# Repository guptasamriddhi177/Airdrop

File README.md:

AIRDROP: Smart Environmental Safety & Early Warning System

It is a smart environmental safety and early-warning system designed to monitor surroundings, detect unusual environmental changes and alert people when something doesn't seem right.

AIRDROP combines multiple sensors, ESP32-based modules and a connected dashboard to make environmental monitoring more accessible. The idea is to build something that doesn't just collect sensor readings but can also help people understand when their surroundings might be becoming unsafe.

I started working on AIRDROP because I wanted to explore how affordable electronics and software could be used for real-world safety problems. I wanted to go beyond making another basic temperature or gas detector, so I started developing a system with multiple monitoring modules, a wearable alert concept and a connected application.

Features

• Environmental monitoring using multiple sensors.
• Temperature, humidity and air-quality monitoring.
• Airflow detection.
• Water-leak detection.
• Motion and distance monitoring.
• ESP32-based wireless communication.
• Firebase integration for real-time data updates.
• Dashboard with sensor readings and alerts.
• Risk scoring system with different safety levels.
• Location-based monitoring concept.
• Wearable notifications and SOS functionality.
• Early-warning and forecasting features under development.

Hardware

AIRDROP uses ESP32-based modules to collect information from different sensors.

Main components:

• ESP32-WROOM-32 modules
• BME680 environmental sensor
• MPU6050 motion sensor
• HC-SR04 ultrasonic sensors
• Airflow sensor
• Water-leak sensors
• Custom-designed PCB
• USB power connection

The system is divided into multiple sensor modules so different environmental parameters can be monitored together.

Schematics

Instead of relying entirely on ready-made sensor boards, I worked on a custom PCB design for the system.

The design uses two ESP32-WROOM-32 modules and a combined board architecture. The goal was to make the electronics more organized and suitable for a proper physical assembly.

PCB specifications:

• 4-layer PCB
• 50 × 50 mm board
• USB-powered design
• Two ESP32-WROOM-32 modules
• Custom component placement and routing

3D Assembly

I also worked on the 3D assembly to understand how the different components would fit together physically.

This helped me visualize the overall structure before moving towards the actual hardware build.

Software & Dashboard

The software side of AIRDROP connects the sensor hardware to a Firebase backend.

The dashboard is designed to display environmental readings, safety scores, alerts and location information.

The planned risk classification is:

- Safe: 0–25
- Caution: 26–50
- Warning: 51–75
- Critical: 76–100

I also want to include a map-based monitoring system, historical readings, multilingual support and a rescue mode.

Firmware

The firmware is being developed for the ESP32 modules.

Its main responsibilities include:

• Reading data from connected sensors.
• Processing sensor readings.
• Communicating between modules.
• Sending data to Firebase.
• Detecting unusual readings.
• Triggering alerts when required.

The idea is to avoid unnecessary panic alerts and make notifications meaningful.

Current Progress

The PCB design and 3D assembly have been worked on, and the dashboard and software architecture are also in development.

I'm currently focusing on firmware, sensor integration and connecting the different parts of the system.

There are still plenty of things to test and improve, especially when it comes to making the hardware and software work together reliably.

Why AIRDROP?

I wanted to build something that could have a practical purpose outside a normal electronics project.

Environmental hazards can affect people without much warning. AIRDROP is my attempt to explore how connected sensors and accessible technology could help detect unusual conditions earlier.

It's still a work in progress, but every part of this project is helping me understand hardware design, embedded systems, software integration and real-world engineering.

Credits & Acknowledgements

AIRDROP is an independently developed project.

Hardware architecture, PCB design, software integration and system planning are part of the project development.

Thanks to the open-source hardware and software communities for the tools, libraries and resources that make projects like this possible.

Built with curiosity, experimentation and a lot of debugging.

AIRDROP: A Safer method

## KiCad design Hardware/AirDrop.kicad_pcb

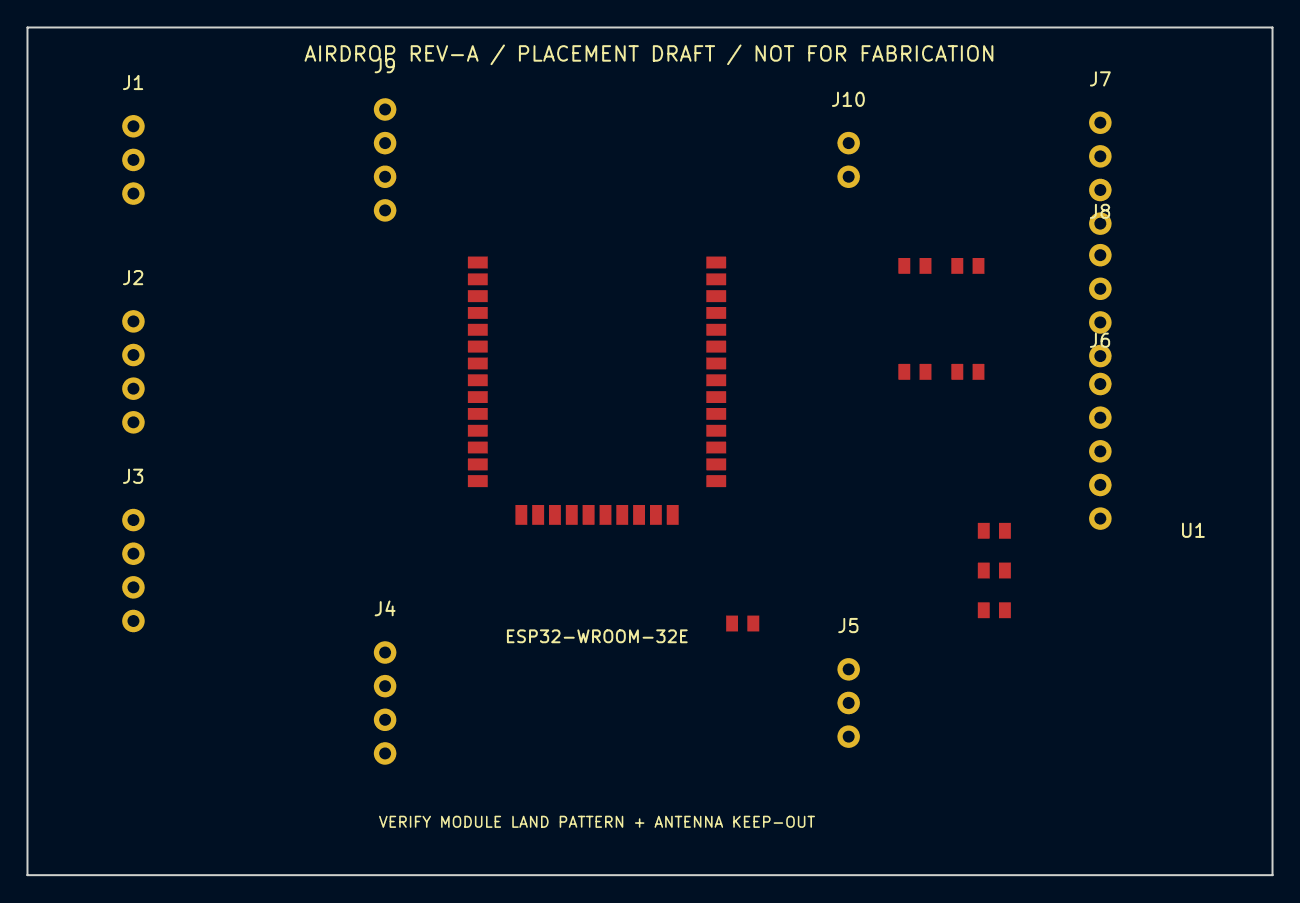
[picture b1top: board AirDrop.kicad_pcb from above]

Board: 4 copper layers, 94.0 x 64.0 mm, 19 parts (0 on the bottom side), 19 nets, no tracks yet.

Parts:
J1: 5V_IN / 3V3_IN / GND; HDR_1x3_P2.54
J2: BME680 I2C MODULE; HDR_1x4_P2.54
J3: MPU6050 I2C MODULE; HDR_1x4_P2.54
J4: INDOOR AIRFLOW I2C; HDR_1x4_P2.54
J5: OUTDOOR ANEMOMETER; HDR_1x3_P2.54
J6: LEAK PROBES Z1-Z3; HDR_1x5_P2.54
J7: ULTRASONIC 1; HDR_1x4_P2.54
J8: ULTRASONIC 2; HDR_1x4_P2.54
J9: UART PROGRAMMING; HDR_1x4_P2.54
J10: RESET / BOOT; HDR_1x2_P2.54
R1: 10k ECHO1 TOP; R_0805
R2: 20k ECHO1 BOT; R_0805
R3: 10k ECHO2 TOP; R_0805
R4: 20k ECHO2 BOT; R_0805
R5: 10k LEAK1 PULLUP; R_0805
R6: 10k LEAK2 PULLUP; R_0805
R7: 10k LEAK3 PULLUP; R_0805
R8: 10k WIND PULLUP; R_0805
U1: ESP32-WROOM-32E (verify land pattern); ESP32-WROOM-32E_PROVISIONAL

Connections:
+3V3: J1.2, J2.1, J3.1, J4.1, J5.1, J6.1, J9.1, R5.1, R6.1, R7.1, R8.1, U1.2
+5V: J1.1, J7.1, J8.1
BOOT: J10.2, U1.25
EN: J10.1, U1.3
GND: J1.3, J2.2, J3.2, J4.2, J5.2, J6.2, J7.2, J8.2, J9.2, R2.2, R4.2, U1.1, U1.15, U1.38
I2C_SCL: J2.4, J3.4, J4.4, U1.36
I2C_SDA: J2.3, J3.3, J4.3, U1.33
LEAK_1: J6.3, R5.2, U1.6
LEAK_2: J6.4, R6.2, U1.7
LEAK_3: J6.5, R7.2, U1.4
UART_RX: J9.4, U1.34
UART_TX: J9.3, U1.35
US1_ECHO_DIV: R1.2, R2.1, U1.12
US1_ECHO_RAW: J7.4, R1.1
US1_TRIG: J7.3, U1.10
US2_ECHO_DIV: R3.2, R4.1, U1.13
US2_ECHO_RAW: J8.4, R3.1
US2_TRIG: J8.3, U1.11
WIND_PULSE: J5.3, R8.2, U1.9

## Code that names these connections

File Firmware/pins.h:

#pragma once
// Provisional ESP32-WROOM-32E GPIO allocation. Verify against module pinout,
// board schematic, boot-strapping requirements and all connected peripherals.
#define PIN_I2C_SDA 21
#define PIN_I2C_SCL 22
#define PIN_WIND_PULSE 33
#define PIN_LEAK_1 34
#define PIN_LEAK_2 35
#define PIN_LEAK_3 36
#define PIN_US1_TRIG 25
#define PIN_US1_ECHO 27
#define PIN_US2_TRIG 26
#define PIN_US2_ECHO 14
// GPIO34-39 are input-only and have no internal pull-ups/pull-downs.
// Add external pull-ups or appropriate interface conditioning on the PCB.
